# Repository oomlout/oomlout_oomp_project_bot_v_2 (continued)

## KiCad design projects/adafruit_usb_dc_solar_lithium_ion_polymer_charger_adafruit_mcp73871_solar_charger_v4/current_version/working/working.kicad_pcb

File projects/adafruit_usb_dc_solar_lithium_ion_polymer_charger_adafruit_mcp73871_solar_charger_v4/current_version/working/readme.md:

# usb_dc_solar_lithium_ion_polymer_charger
 
## summary 
* id: adafruit_usb_dc_solar_lithium_ion_polymer_charger_adafruit_mcp73871_solar_charger_v4
* user: adafruit
* name: usb_dc_solar_lithium_ion_polymer_charger
* board: adafruit_mcp73871_solar_charger_v4
* repo: https://github.com/adafruit/USB-DC-Solar-Lithium-Ion-Polymer-charger

* src_file_repo_sch: 
* src_file_repo_sch_link: https://github.com/adafruit/USB-DC-Solar-Lithium-Ion-Polymer-charger/tree/master/
* full details link: https://github.com/oomlout/oomlout_oomp_project_bot_v_2/tree/main/projects/adafruit_usb_dc_solar_lithium_ion_polymer_charger_adafruit_mcp73871_solar_charger_v4/current_version/working  

## schematic  
  
[schematic (pdf)](working_schematic.pdf) 

## pcb  

[board (pdf)](working.pdf)  

## working_bom
| Id | Designator | Footprint | Quantity | Designation | Supplier and ref |  | None | 
| --- | --- | --- | --- | --- | --- | --- | --- | 
| 1 | R9,R8,R10 | R0805 | 3 | 1K |  |  | [''] | 
| 2 | CN4 | USB-MINIB_LARGER | 1 |  |  |  | [''] | 
| 3 | JP3 | 1X02_ROUND | 1 | LOAD |  |  | [''] | 
| 4 | U$2,U$3,U$8 | FIDUCIAL_1MM | 3 | FIDUCIAL |  |  | [''] | 
| 5 | RT2 | M0805 | 1 | 150K |  |  | [''] | 
| 6 | PWR0 | CHIPLED_0805_NOOUTLINE | 1 | RED |  |  | [''] | 
| 7 | DONE0 | CHIPLED_0805_NOOUTLINE | 1 | GREEN |  |  | [''] | 
| 8 | R11 | 0805-THM | 1 | 2K |  |  | [''] | 
| 9 | U$7,U$5,U$6,U$4 | MOUNTINGHOLE_2.5_PLATED | 4 | MOUNTINGHOLE2.5 |  |  | [''] | 
| 10 | IC1 | QFN20_4MM | 1 | MCP73871 |  |  | [''] | 
| 11 | C1,C2,C3 | C0805K | 3 | 10uF |  |  | [''] | 
| 12 | R5 | M0805 | 1 | 1K |  |  | [''] | 
| 13 | R2 | R0805 | 1 | 270K |  |  | [''] | 
| 14 | D1 | SOD-123 | 1 | MBR120VLSFT1G |  |  | [''] | 
| 15 | CN1 | DCJACK_2MM_SMT | 1 | DCIN |  |  | [''] | 
| 16 | LOAD0,BATT0 | JST-PH-2-SMT-RA | 2 |  |  |  | [''] | 
| 17 | R12,R3 | R0805 | 2 | 100K |  |  | [''] | 
| 18 | JP1 | 1X02_OVAL | 1 | DCIN |  |  | [''] | 
| 19 | CHRG/LBO0 | CHIPLED_0805_NOOUTLINE | 1 | ORANGE |  |  | [''] | 
| 20 | C4 | E5-13 | 1 | 4700uF/10V |  |  | [''] | 
| 21 | JP4 | 1X02_ROUND | 1 | BATT |  |  | [''] | 
| 22 | THERM0 | 0805-THM | 1 | 10K |  |  | [''] | 
| 23 | JP5 | 1X03-CLEANBIG | 1 |  |  |  | [''] | 
| 24 | R1 | R0805 | 1 | 0 |  |  | [''] | 
| 25 | U$1 | ADAFRUIT_TEXT_20MM | 1 |  |  |  | [''] | 

## bom_schematic
| Ref | Qnty | Value | Cmp name | Footprint | Description | Vendor | DNP | 
| --- | --- | --- | --- | --- | --- | --- | --- | 
| BATT0 | 1 | JST_2PIN-SMT-RA | JST_2PIN-SMT-RA | working:JST-PH-2-SMT-RA |  |  |  | 
| C1, C2, C3 | 3 | 10uF | C-USC0805K | working:C0805K |  |  |  | 
| C4 | 1 | 4700uF/10V | CPOL-USE5-13 | working:E5-13 |  |  |  | 
| CHRG/LBO0 | 1 | ORANGE | LED0805_NOOUTLINE | working:CHIPLED_0805_NOOUTLINE |  |  |  | 
| CN1 | 1 | DCIN | DCBARRELSMT | working:DCJACK_2MM_SMT |  |  |  | 
| CN4 | 1 | USBMINIBLARGE | USBMINIBLARGE | working:USB-MINIB_LARGER |  |  |  | 
| D1 | 1 | MBR120VLSFT1G | DIODESOD-123 | working:SOD-123 |  |  |  | 
| DONE0 | 1 | GREEN | LED0805_NOOUTLINE | working:CHIPLED_0805_NOOUTLINE |  |  |  | 
| IC1 | 1 | MCP73871 | MCP73871 | working:QFN20_4MM |  |  |  | 
| JP1 | 1 | DCIN | HEADER-1X2 | working:1X02_OVAL |  |  |  | 
| JP3 | 1 | LOAD | HEADER-1X2ROUND | working:1X02_ROUND |  |  |  | 
| JP4 | 1 | BATT | HEADER-1X2ROUND | working:1X02_ROUND |  |  |  | 
| JP5 | 1 | PINHD-1X3CB | PINHD-1X3CB | working:1X03-CLEANBIG |  |  |  | 
| LOAD0 | 1 | JST_2PIN-SMT-RA | JST_2PIN-SMT-RA | working:JST-PH-2-SMT-RA |  |  |  | 
| PWR0 | 1 | RED | LED0805_NOOUTLINE | working:CHIPLED_0805_NOOUTLINE |  |  |  | 
| R1 | 1 | 0 | R-US_R0805 | working:R0805 |  |  |  | 
| R2 | 1 | 270K | R-US_R0805 | working:R0805 |  |  |  | 
| R3, R12 | 2 | 100K | R-US_R0805 | working:R0805 |  |  |  | 
| R5 | 1 | 1K | R-US_M0805 | working:M0805 |  |  |  | 
| R8, R9, R10 | 3 | 1K | R-US_R0805 | working:R0805 |  |  |  | 
| R11 | 1 | 2K | R-US_FLIPFLOP | working:0805-THM |  |  |  | 
| RT2 | 1 | 150K | R-US_M0805 | working:M0805 |  |  |  | 
| THERM0 | 1 | 10K | R-US_FLIPFLOP | working:0805-THM |  |  |  | 
| U$2, U$3, U$8 | 3 | FIDUCIAL | FIDUCIAL | working:FIDUCIAL_1MM |  |  |  | 
| U$4, U$5, U$6, U$7 | 4 | MOUNTINGHOLE2.5 | MOUNTINGHOLE2.5 | working:MOUNTINGHOLE_2.5_PLATED |  |  |  | 

## mounting_holes
| x | y | package | value | ref | size | 
| --- | --- | --- | --- | --- | --- | 
| 0.0 | 0.0 | MOUNTINGHOLE_2.5_PLATED | MOUNTINGHOLE2.5 | U$4 | m3 | 
| 35.56 | 0.0 | MOUNTINGHOLE_2.5_PLATED | MOUNTINGHOLE2.5 | U$5 | m3 | 
| 0.0 | 25.4 | MOUNTINGHOLE_2.5_PLATED | MOUNTINGHOLE2.5 | U$6 | m3 | 
| 35.56 | 25.4 | MOUNTINGHOLE_2.5_PLATED | MOUNTINGHOLE2.5 | U$7 | m3 |

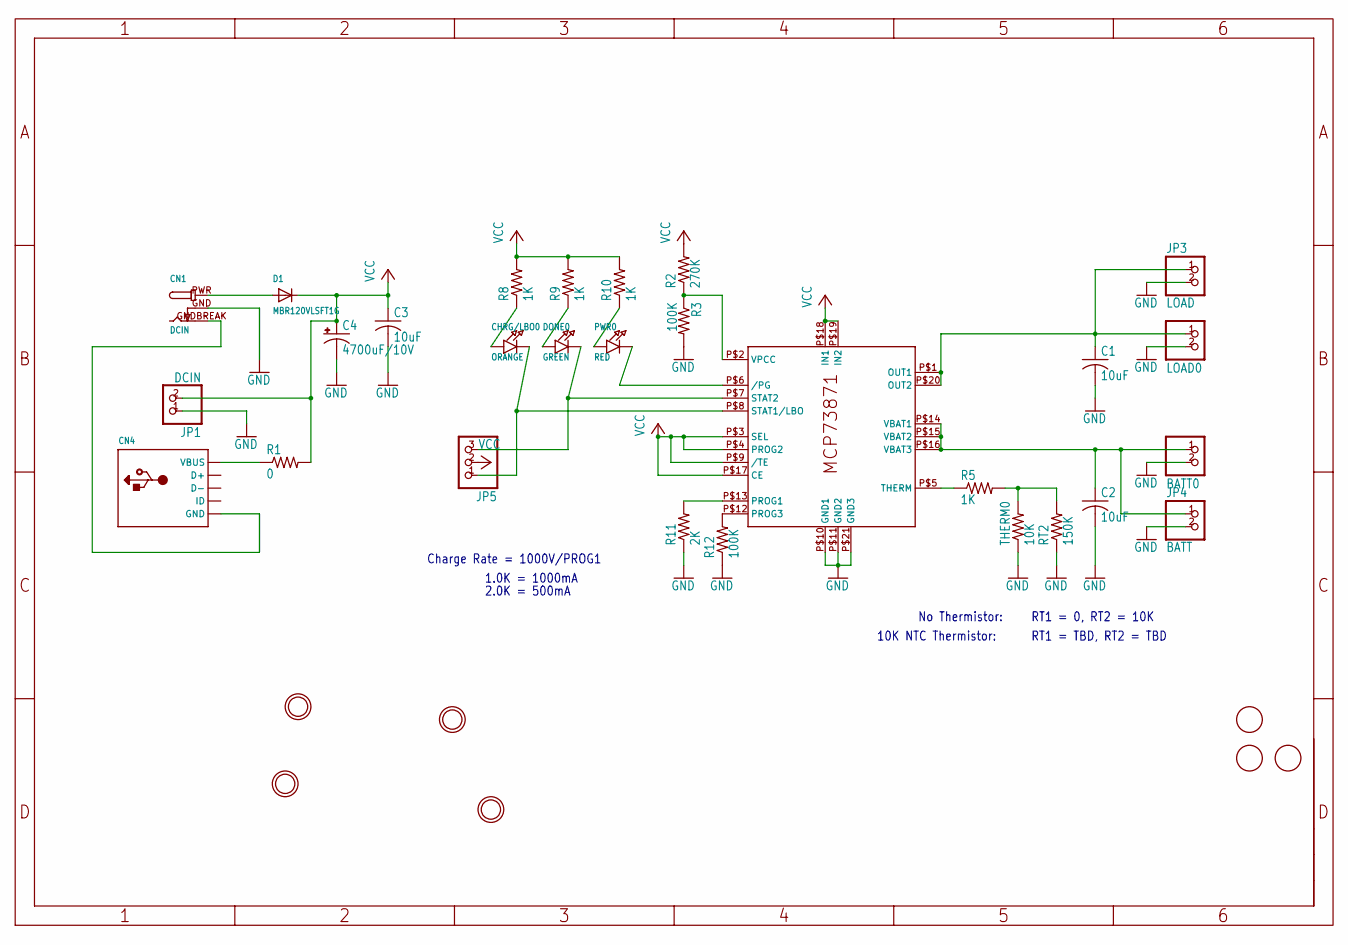
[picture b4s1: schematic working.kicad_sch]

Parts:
BATT0: JST_2PIN-SMT-RA; JST-PH-2-SMT-RA
C1, C2, C3: 10uF; C0805K
C4: 4700uF/10V; E5-13
CHRG/LBO0: ORANGE; CHIPLED_0805_NOOUTLINE
CN1: DCIN; DCJACK_2MM_SMT
CN4: USBMINIBLARGE; USB-MINIB_LARGER
D1: MBR120VLSFT1G; SOD-123
DONE0: GREEN; CHIPLED_0805_NOOUTLINE
IC1: MCP73871; QFN20_4MM
JP1: DCIN; 1X02_OVAL
JP3: LOAD; 1X02_ROUND
JP4: BATT; 1X02_ROUND
JP5: PINHD-1X3CB; 1X03-CLEANBIG
LOAD0: JST_2PIN-SMT-RA; JST-PH-2-SMT-RA
PWR0: RED; CHIPLED_0805_NOOUTLINE
R1: 0; R0805
R2: 270K; R0805
R3, R12: 100K; R0805
R5: 1K; M0805
R8, R9, R10: 1K; R0805
R11: 2K; 0805-THM
RT2: 150K; M0805
THERM0: 10K; 0805-THM
U$2, U$3, U$8: FIDUCIAL; FIDUCIAL_1MM
U$4, U$5, U$6, U$7: MOUNTINGHOLE2.5; MOUNTINGHOLE_2.5_PLATED

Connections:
BATT: BATT0.1 (2), C2.1, IC1.P$14 (VBAT1), IC1.P$15 (VBAT2), IC1.P$16 (VBAT3), JP4.1
GND: BATT0.2 (1), C1.2, C2.2, C3.2, C4.-, CN1.GND (GNDBREAK), IC1.P$10 (GND1), IC1.P$11 (GND2), IC1.P$21 (GND3), JP1.1, JP3.2, JP4.2, LOAD0.2 (1), R3.2, R11.1, R12.1, RT2.1, THERM0.1
unnamed: IC1.P$6 (/PG), PWR0.C
unnamed: CN4.VBUS, R1.1
unnamed: CN1.GNDBREAK (GND), CN4.GND, CN4.GND1 (GND), CN4.GND2 (GND), CN4.GND3 (GND), CN4.GND4 (GND)
unnamed: DONE0.C, IC1.P$7 (STAT2), JP5.3
unnamed: IC1.P$5 (THERM), R5.1
unnamed: IC1.P$2 (VPCC), R2.1, R3.1
unnamed: R5.2, RT2.2, THERM0.2
unnamed: CN1.PWR, D1.A
unnamed: CHRG/LBO0.C, IC1.P$8 (STAT1/LBO), JP5.1
unnamed: CHRG/LBO0.A, R8.1
unnamed: DONE0.A, R9.1
unnamed: PWR0.A, R10.1
unnamed: IC1.P$12 (PROG3), R12.2
unnamed: IC1.P$13 (PROG1), R11.2
OUT: C1.1, IC1.P$1 (OUT1), IC1.P$20 (OUT2), JP3.1, LOAD0.1 (2)
VCC: C3.1, C4.+, D1.C, IC1.P$3 (SEL), IC1.P$4 (PROG2), IC1.P$9 (/TE), IC1.P$17 (CE), IC1.P$18 (IN1), IC1.P$19 (IN2), JP1.2, JP5.2, R1.2, R2.2, R8.2, R9.2, R10.2

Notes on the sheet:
RT1 = 0, RT2 = 10K
RT1 = TBD, RT2 = TBD
10K NTC Thermistor:
1.0K = 1000mA
Charge Rate = 1000V/PROG1
No Thermistor:
2.0K = 500mA

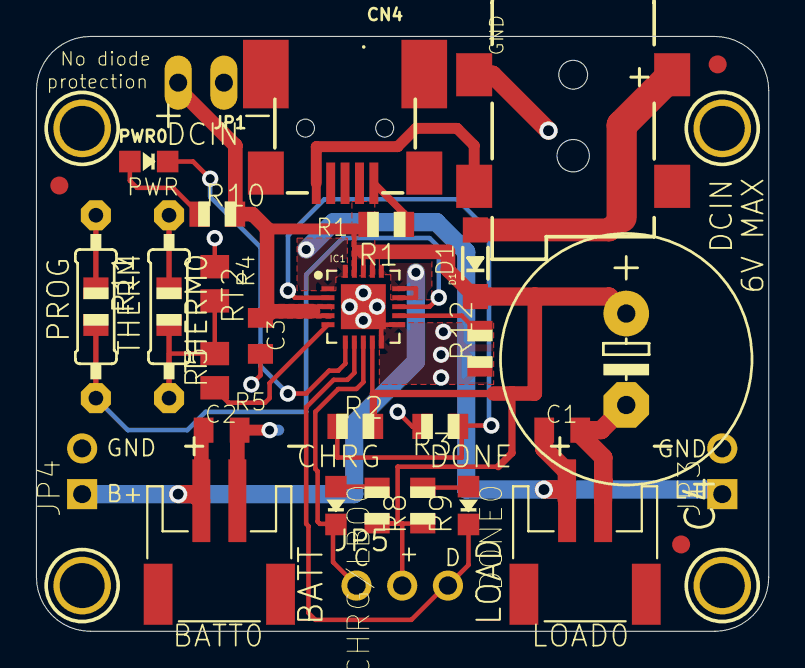
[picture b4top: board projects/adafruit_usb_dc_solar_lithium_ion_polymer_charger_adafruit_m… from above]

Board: 16 copper layers, 40.7 x 33.0 mm, 36 parts (1 on the bottom side), 18 nets.

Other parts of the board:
U$1: ADAFRUIT_TEXT_20MM

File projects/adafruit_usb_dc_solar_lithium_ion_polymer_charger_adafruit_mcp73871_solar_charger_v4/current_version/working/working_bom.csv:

"Id";"Designator";"Footprint";"Quantity";"Designation";"Supplier and ref";
1;"R9,R8,R10";"R0805";3;"1K";;;
2;"CN4";"USB-MINIB_LARGER";1;"";;;
3;"JP3";"1X02_ROUND";1;"LOAD";;;
4;"U$2,U$3,U$8";"FIDUCIAL_1MM";3;"FIDUCIAL";;;
5;"RT2";"M0805";1;"150K";;;
6;"PWR0";"CHIPLED_0805_NOOUTLINE";1;"RED";;;
7;"DONE0";"CHIPLED_0805_NOOUTLINE";1;"GREEN";;;
8;"R11";"0805-THM";1;"2K";;;
9;"U$7,U$5,U$6,U$4";"MOUNTINGHOLE_2.5_PLATED";4;"MOUNTINGHOLE2.5";;;
10;"IC1";"QFN20_4MM";1;"MCP73871";;;
11;"C1,C2,C3";"C0805K";3;"10uF";;;
12;"R5";"M0805";1;"1K";;;
13;"R2";"R0805";1;"270K";;;
14;"D1";"SOD-123";1;"MBR120VLSFT1G";;;
15;"CN1";"DCJACK_2MM_SMT";1;"DCIN";;;
16;"LOAD0,BATT0";"JST-PH-2-SMT-RA";2;"";;;
17;"R12,R3";"R0805";2;"100K";;;
18;"JP1";"1X02_OVAL";1;"DCIN";;;
19;"CHRG/LBO0";"CHIPLED_0805_NOOUTLINE";1;"ORANGE";;;
20;"C4";"E5-13";1;"4700uF/10V";;;
21;"JP4";"1X02_ROUND";1;"BATT";;;
22;"THERM0";"0805-THM";1;"10K";;;
23;"JP5";"1X03-CLEANBIG";1;"";;;
24;"R1";"R0805";1;"0";;;
25;"U$1";"ADAFRUIT_TEXT_20MM";1;"";;;

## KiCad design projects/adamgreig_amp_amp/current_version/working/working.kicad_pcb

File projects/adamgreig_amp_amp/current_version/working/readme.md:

# amp
 
## summary 
* id: adamgreig_amp_amp
* user: adamgreig
* name: amp
* board: amp
* repo: https://github.com/adamgreig/amp
* src_file_repo_kicad_pcb: amp.kicad_pcb
* src_file_repo_kicad_pcb_link: https://github.com/adamgreig/amp/tree/master/amp.kicad_pcb

* src_file_repo_sch: amp.sch
* src_file_repo_sch_link: https://github.com/adamgreig/amp/tree/master/amp.sch
* full details link: https://github.com/oomlout/oomlout_oomp_project_bot_v_2/tree/main/projects/adamgreig_amp_amp/current_version/working  

## schematic  
  
[schematic (pdf)](working_schematic.pdf) 

## pcb  

[board (pdf)](working.pdf)  

## working_bom
| Id | Designator | Footprint | Quantity | Designation | Supplier and ref |  | None | 
| --- | --- | --- | --- | --- | --- | --- | --- | 
| 1 | C1 | 0603 | 1 | 4Âµ7 |  |  | [''] | 
| 2 | C2,C10,C11 | 0603 | 3 | 1Âµ |  |  | [''] | 
| 3 | C3,C4,C5,C8 | 0402 | 4 | 100n |  |  | [''] | 
| 4 | C6 | 0402 | 1 | 10n |  |  | [''] | 
| 5 | C7,C9 | 0402 | 2 | 15p |  |  | [''] | 
| 6 | IC1 | QFN-48-EP-ST | 1 | STM32F103CBU6 |  |  | [''] | 
| 7 | IC2 | SOT-23 | 1 | MCP1700 |  |  | [''] | 
| 8 | J2 | MICROUSB_MOLEX_47589-0001 | 1 | MICROUSB |  |  | [''] | 
| 9 | P1 | TC2030-NL | 1 | SWD_TC |  |  | [''] | 
| 10 | Q1 | SOT-23 | 1 | FDV304P |  |  | [''] | 
| 11 | R1,R6 | 0402 | 2 | 4k7 |  |  | [''] | 
| 12 | R2,R7 | 0402 | 2 | 10k |  |  | [''] | 
| 13 | R3 | 0402 | 1 | 1k5 |  |  | [''] | 
| 14 | R4,R5 | 0402 | 2 | 22 |  |  | [''] | 
| 15 | Y1 | XTAL-50x32 | 1 | 8MHz |  |  | [''] | 
| 16 | P2 | FTSH-105-01-L-DV-K | 1 | SWD |  |  | [''] | 
| 17 | J1 | SM04B-PASS | 1 | SERIAL |  |  | [''] | 

## bom_schematic
| Ref | Qnty | Value | Cmp name | Footprint | Description | Vendor | DNP | 
| --- | --- | --- | --- | --- | --- | --- | --- | 
| C1 | 1 | 4Âµ7 | C | agg:0603 |  |  |  | 
| C2, C10, C11 | 3 | 1Âµ | C | agg:0603 |  |  |  | 
| C3, C4, C5, C8 | 4 | 100n | C | agg:0402 |  |  |  | 
| C6 | 1 | 10n | C | agg:0402 |  |  |  | 
| C7, C9 | 2 | 33p | C | agg:0402 |  |  |  | 
| IC1 | 1 | STM32F103CBU6 | STM32F1xxCxUx | agg:QFN-48-EP-ST |  |  |  | 
| IC2 | 1 | MCP1700 | MCP1700 | agg:SOT-23 |  |  |  | 
| J1 | 1 | SERIAL | CONN_01x04 | agg:SM04B-PASS |  |  |  | 
| J2 | 1 | MICROUSB | MICROUSB | agg:MICROUSB_MOLEX_47589-0001 |  |  |  | 
| P1 | 1 | SWD_TC | SWD_TC | agg:TC2030-NL |  |  |  | 
| P2 | 1 | SWD | SWD | agg:FTSH-105-01-L-DV-K |  |  |  | 
| Q1 | 1 | FDV304P | PFET | agg:SOT-23 |  |  |  | 
| R1, R6 | 2 | 4k7 | R | agg:0402 |  |  |  | 
| R2, R7 | 2 | 10k | R | agg:0402 |  |  |  | 
| R3 | 1 | 1k5 | R | agg:0402 |  |  |  | 
| R4, R5 | 2 | 22 | R | agg:0402 |  |  |  | 
| Y1 | 1 | 8MHz | XTAL | agg:XTAL-50x32 |  |  |  |

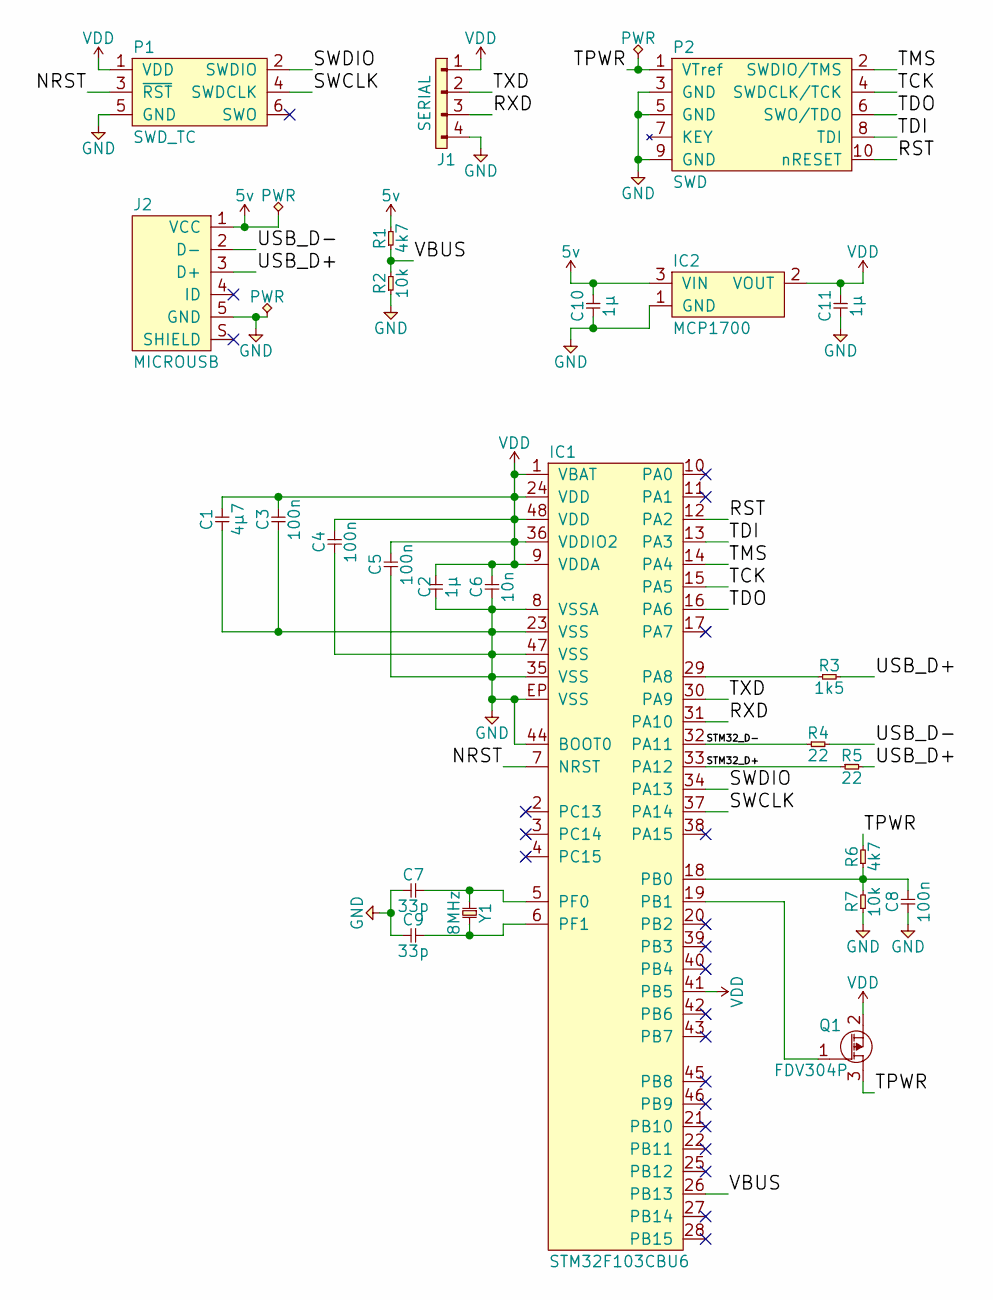
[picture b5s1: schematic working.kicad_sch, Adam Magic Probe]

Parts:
C1: 4µ7; 0603; Farnell 2496930
C2, C10, C11: 1µ; 0603; Farnell 2496916
C3, C4, C5, C8: 100n; 0402; Farnell 1759380
C6: 10n; 0402; Farnell 1758924
C7, C9: 33p; 0402; Farnell 1758955
IC1: STM32F103CBU6; QFN-48-EP-ST; Farnell 2060891
IC2: MCP1700; SOT-23; Farnell 1296592
J1: SERIAL; SM04B-PASS; Farnell 2399347
J2: MICROUSB; MICROUSB_MOLEX_47589-0001; Farnell 1568023
P1: SWD_TC; TC2030-NL
P2: SWD; FTSH-105-01-L-DV-K
Q1: FDV304P; SOT-23; Farnell 9846123
R1, R6: 4k7; 0402; Farnell 2447187
R2, R7: 10k; 0402; Farnell 2447096
R3: 1k5; 0402; Farnell 2447125
R4, R5: 22; 0402; Farnell 2447138
Y1: 8MHz; XTAL-50x32; Farnell 2101329

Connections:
5v: C10.2, IC2.3 (VIN), J2.1 (VCC), R1.2
/NRST: IC1.7 (NRST), P1.3 (~RST)
/RST: IC1.12 (PA2), P2.10 (nRESET)
/RXD: IC1.31 (PA10), J1.3
/STM32_D+: IC1.33 (PA12), R5.1
/STM32_D-: IC1.32 (PA11), R4.1
/SWCLK: IC1.37 (PA14), P1.4 (SWDCLK)
/SWDIO: IC1.34 (PA13), P1.2 (SWDIO)
/TCK: IC1.15 (PA5), P2.4 (SWDCLK/TCK)
/TDI: IC1.13 (PA3), P2.8 (TDI)
/TDO: IC1.16 (PA6), P2.6 (SWO/TDO)
/TMS: IC1.14 (PA4), P2.2 (SWDIO/TMS)
/TPWR: P2.1 (VTref), Q1.3 (D), R6.2
/TXD: IC1.30 (PA9), J1.2
/USB_D+: J2.3 (D+), R3.2, R5.2
/USB_D-: J2.2 (D-), R4.2
/VBUS: IC1.26 (PB13), R1.1, R2.2
GND: C1.1, C2.1, C3.1, C4.1, C5.1, C6.1, C7.1, C8.1, C9.1, C10.1, C11.1, IC1.8 (VSSA), IC1.23 (VSS), IC1.35 (VSS), IC1.44 (BOOT0), IC1.47 (VSS), IC1.EP (VSS), IC2.1 (GND), J1.4, J2.5 (GND), P1.5 (GND), P2.3 (GND), P2.5 (GND), P2.9 (GND), R2.1, R7.1
unnamed: C7.2, IC1.5 (PF0), Y1.1
unnamed: C8.2, IC1.18 (PB0), R6.1, R7.2
unnamed: C9.2, IC1.6 (PF1), Y1.2
unnamed: IC1.19 (PB1), Q1.1 (G)
unnamed: IC1.29 (PA8), R3.1
VDD: C1.2, C2.2, C3.2, C4.2, C5.2, C6.2, C11.2, IC1.1 (VBAT), IC1.9 (VDDA), IC1.24 (VDD), IC1.36 (VDDIO2), IC1.41 (PB5), IC1.48 (VDD), IC2.2 (VOUT), J1.1, P1.1 (VDD), Q1.2 (S)

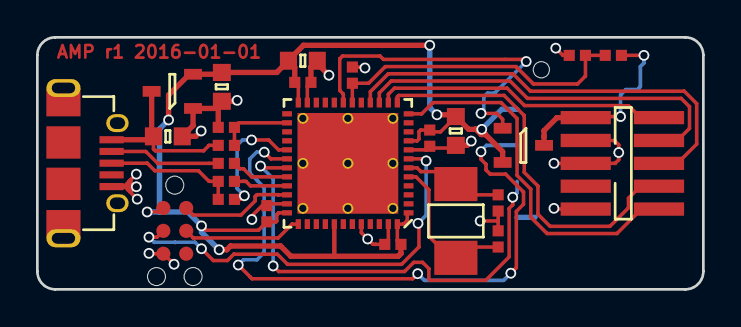
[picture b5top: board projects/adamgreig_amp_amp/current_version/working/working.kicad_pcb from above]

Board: 2 copper layers, 37.0 x 14.0 mm, 26 parts (1 on the bottom side), 24 nets.
